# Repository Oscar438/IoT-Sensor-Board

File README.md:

# IoT-Sensor-Board

Eagle uses project files, these are kind of like eagle specific folders where it stores boards and schematics. To use the Git repo you'll want
to add the directory to your eagle path. Go to options>directories and add the gitlibrary folder, and project folder by pasting the path. You 
can add multiple paths by using the semicolon (;)

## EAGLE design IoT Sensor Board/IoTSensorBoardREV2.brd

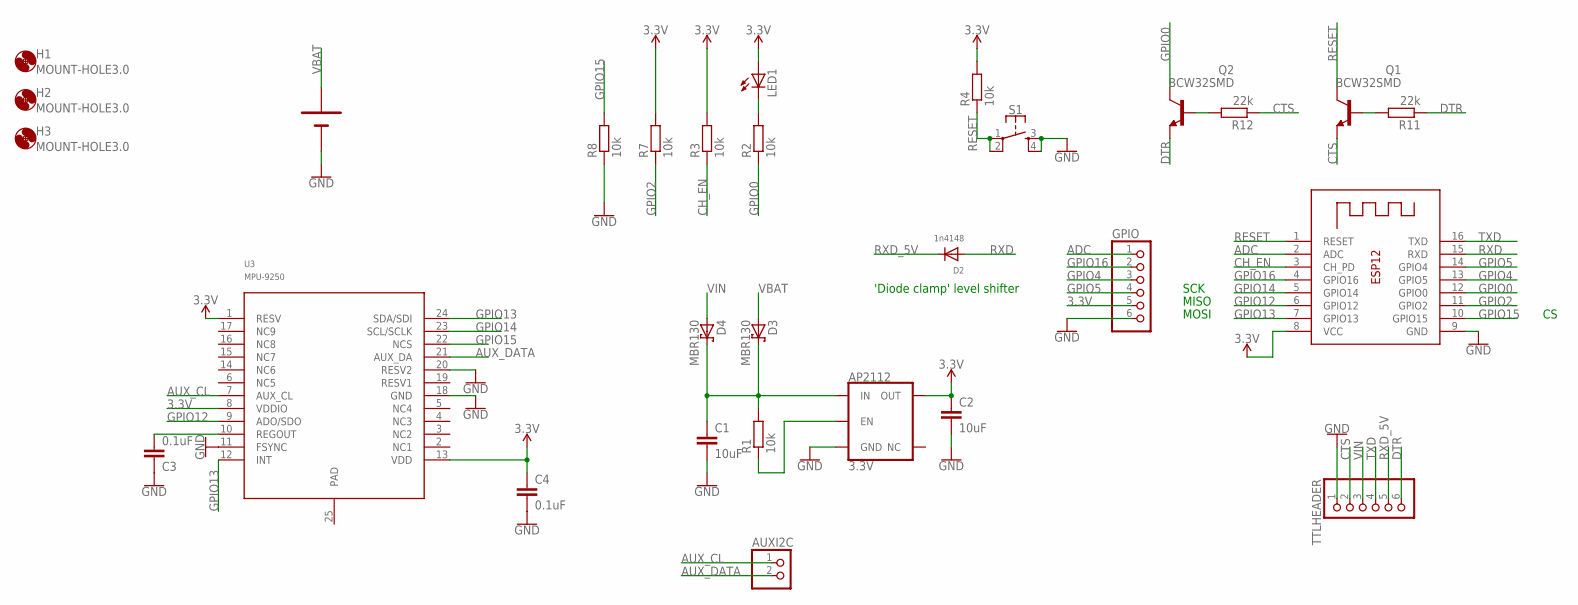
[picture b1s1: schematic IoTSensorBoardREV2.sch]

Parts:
AP2112: 3.3V; SOT23-5
AUXI2C: PINHD-1X2; 1X02
C1, C2: 10uF; C0805
C3, C4: 0.1uF; C0805
D2: 1n4148; SMADIODE
D3, D4: MBR130; SMB
ESP-12: ESP-12
GPIO: PINHD-1X6; 1X06
H1, H2, H3: MOUNT-HOLE3.0; 3,0
LED1: LEDCHIP-LED0805; CHIP-LED0805
Q1, Q2: BCW32SMD; SOT23-BEC
R1, R2, R3, R4, R7, R8: 10k; R0805
R11, R12: 22k; R0805
S1: MOMENTARY-SWITCH-SPST-2-SMD-5.2MM; TACTILE_SWITCH_SMD_5.2MM
TTLHEADER: PINHD-1X6; 1X06
U3: MPU-9250; LEAD-QFN24
U$1: SMTU_2450N

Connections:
3.3V: AP2112.5 (OUT), C2.1, C4.1, ESP-12.8 (VCC), GPIO.5, LED1.A, R3.2, R4.2, R7.2, U3.1 (RESV), U3.8 (VDDIO), U3.13 (VDD)
ADC: ESP-12.2 (ADC), GPIO.1
AUX_CL: AUXI2C.1, U3.7 (AUX_CL)
AUX_DATA: AUXI2C.2, U3.21 (AUX_DA)
CH_EN: ESP-12.3 (CH_PD), R3.1
CTS: Q1.E, R12.1, TTLHEADER.2
DTR: Q2.E, R11.1, TTLHEADER.6
GND: AP2112.2 (GND), C1.2, C2.2, C3.1, C4.2, ESP-12.9 (GND), GPIO.6, R8.1, S1.3, S1.4, TTLHEADER.1, U3.11 (FSYNC), U3.18 (GND), U3.20 (RESV2), U$1.P$1 (P$1N)
GPIO0: ESP-12.12 (GPIO0), Q2.C, R2.1
GPIO2: ESP-12.11 (GPIO2), R7.1
GPIO4: ESP-12.13 (GPIO5), GPIO.3
GPIO5: ESP-12.14 (GPIO4), GPIO.4
GPIO12: ESP-12.6 (GPIO12), U3.9 (ADO/SDO)
GPIO13: ESP-12.7 (GPIO13), U3.12 (INT), U3.24 (SDA/SDI)
GPIO14: ESP-12.5 (GPIO14), U3.23 (SCL/SCLK)
GPIO15: ESP-12.10 (GPIO15), R8.2, U3.22 (NCS)
GPIO16: ESP-12.4 (GPIO16), GPIO.2
unnamed: AP2112.3 (EN), R1.1
unnamed: AP2112.1 (IN), C1.1, D3.C, D4.C, R1.2
unnamed: LED1.C, R2.2
unnamed: C3.2, U3.10 (REGOUT)
unnamed: Q2.B, R12.2
unnamed: Q1.B, R11.2
RESET: ESP-12.1 (RESET), Q1.C, R4.1, S1.1, S1.2
RXD: D2.A, ESP-12.15 (RXD)
RXD_5V: D2.C, TTLHEADER.5
TXD: ESP-12.16 (TXD), TTLHEADER.4
VBAT: D3.A, U$1.P$2 (P$2P)
VIN: D4.A, TTLHEADER.3

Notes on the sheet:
'Diode clamp' level shifter
SCK
MISO
MOSI

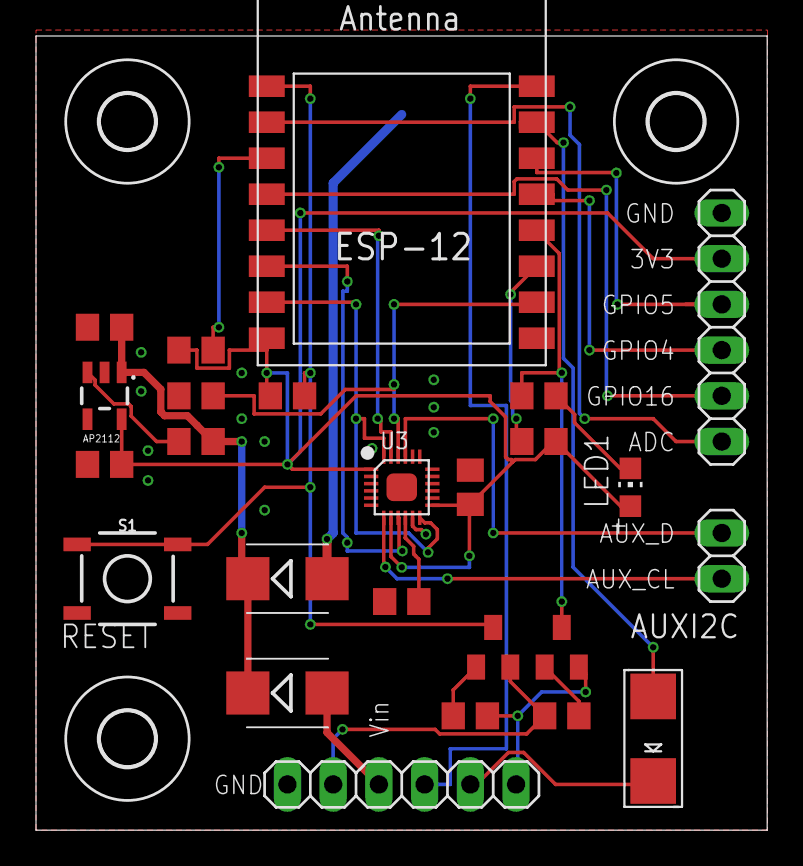
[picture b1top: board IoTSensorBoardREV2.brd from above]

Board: 2 copper layers, 40.6 x 44.1 mm, 29 parts (1 on the bottom side), 29 nets.

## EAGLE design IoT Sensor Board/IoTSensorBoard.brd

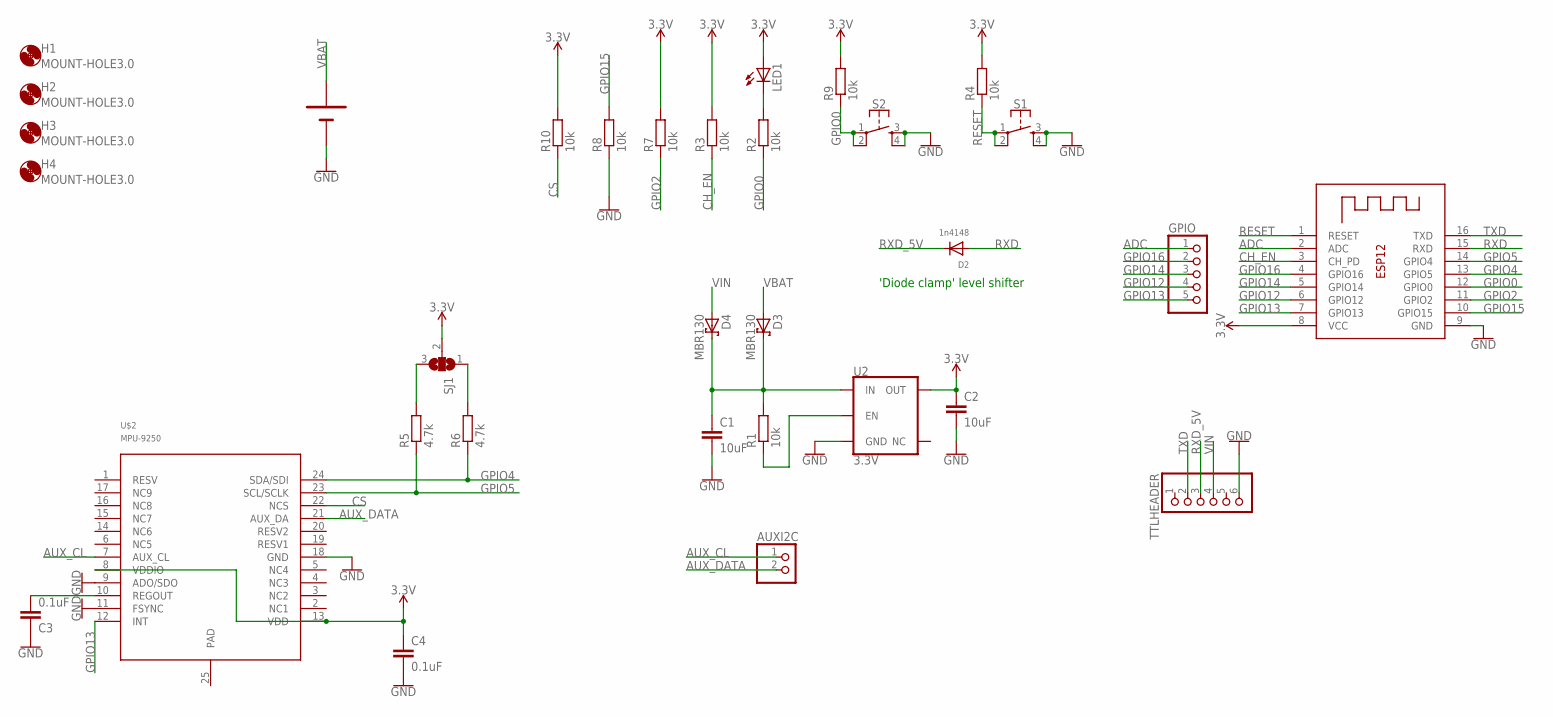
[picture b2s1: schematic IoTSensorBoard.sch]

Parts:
AUXI2C: PINHD-1X2; 1X02
C1, C2: 10uF; C0805
C3, C4: 0.1uF; C0805
D2: 1n4148; SMADIODE
D3, D4: MBR130; SMB
GPIO: PINHD-1X5; 1X05
H1, H2, H3, H4: MOUNT-HOLE3.0; 3,0
LED1: LEDCHIP-LED0805; CHIP-LED0805
R1, R2, R3, R4, R7, R8, R9, R10: 10k; R0805
R5, R6: 4.7k; R0805
S1, S2: MOMENTARY-SWITCH-SPST-2-SMD-5.2MM; TACTILE_SWITCH_SMD_5.2MM
SJ1: SJ2W; SJ_2
TTLHEADER: PINHD-1X6; 1X06
U2: 3.3V; SOT23-5
U$1: SMTU_2450N
U$2: MPU-9250; LEAD-QFN24
X1: ESP-12

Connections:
3.3V: C2.1, C4.1, LED1.A, R3.2, R4.2, R7.2, R9.2, R10.2, SJ1.2, U2.5 (OUT), U$2.8 (VDDIO), U$2.13 (VDD), X1.8 (VCC)
ADC: GPIO.1, X1.2 (ADC)
AUX_CL: AUXI2C.1, U$2.7 (AUX_CL)
AUX_DATA: AUXI2C.2, U$2.21 (AUX_DA)
CH_EN: R3.1, X1.3 (CH_PD)
CS: R10.1, U$2.22 (NCS)
GND: C1.2, C2.2, C3.1, C4.2, R8.1, S1.3, S1.4, S2.3, S2.4, TTLHEADER.6, U2.2 (GND), U$1.P$1 (P$1N), U$2.9 (ADO/SDO), U$2.11 (FSYNC), U$2.18 (GND), X1.9 (GND)
GPIO0: R2.1, R9.1, S2.1, S2.2, X1.12 (GPIO0)
GPIO2: R7.1, X1.11 (GPIO2)
GPIO4: R6.1, U$2.24 (SDA/SDI), X1.13 (GPIO5)
GPIO5: R5.1, U$2.23 (SCL/SCLK), X1.14 (GPIO4)
GPIO12: GPIO.4, X1.6 (GPIO12)
GPIO13: GPIO.5, U$2.12 (INT), X1.7 (GPIO13)
GPIO14: GPIO.3, X1.5 (GPIO14)
GPIO15: R8.2, X1.10 (GPIO15)
GPIO16: GPIO.2, X1.4 (GPIO16)
unnamed: R1.1, U2.3 (EN)
unnamed: C1.1, D3.C, D4.C, R1.2, U2.1 (IN)
unnamed: LED1.C, R2.2
unnamed: R5.2, SJ1.3
unnamed: C3.2, U$2.10 (REGOUT)
unnamed: R6.2, SJ1.1
RESET: R4.1, S1.1, S1.2, X1.1 (RESET)
RXD: D2.A, X1.15 (RXD)
RXD_5V: D2.C, TTLHEADER.3
TXD: TTLHEADER.2, X1.16 (TXD)
VBAT: D3.A, U$1.P$2 (P$2P)
VIN: D4.A, TTLHEADER.4

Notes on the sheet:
'Diode clamp' level shifter

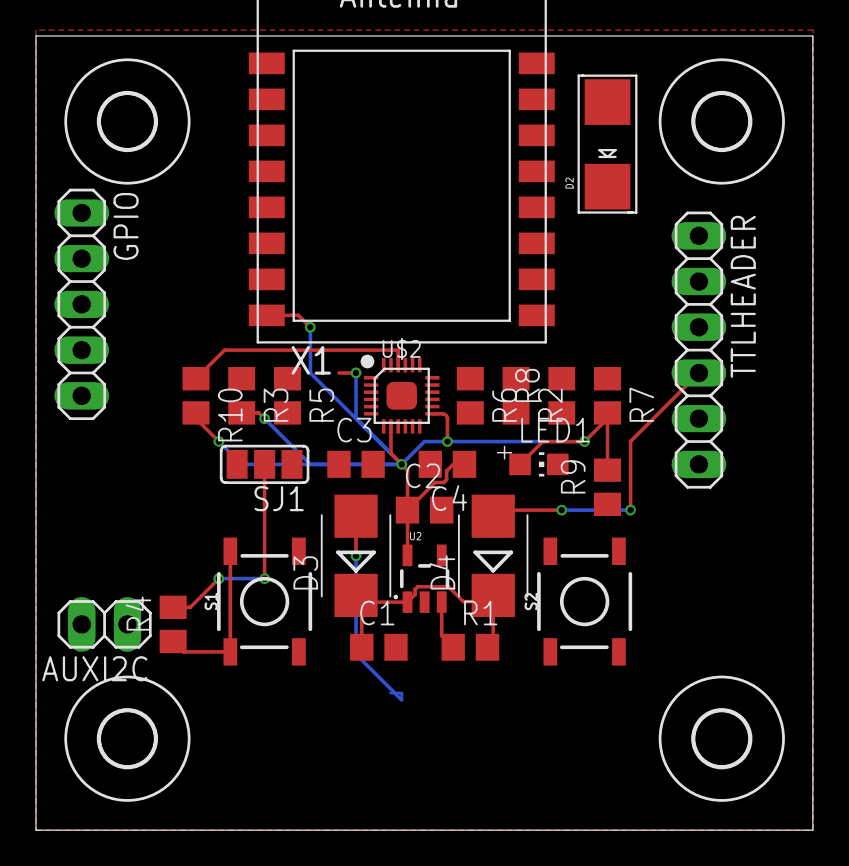
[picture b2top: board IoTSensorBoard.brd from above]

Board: 2 copper layers, 43.2 x 44.1 mm, 32 parts (1 on the bottom side), 28 nets.

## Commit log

2018-05-01 First commit
    Initial commit using eagle files, sparkfun libraries included along with an IoT Custom library for any parts we might need to make ourselves
2018-05-01 Edited readme
2018-05-01 ESP8266 board mostly done schematic wise
2018-05-02 Alain Testing Git
    Added a rubbish .brd file
2018-05-03 Schematic completed
    I had to change the MPU part, the sparkfun version had a chip that wouldn't play nice on the PCB
2018-05-03 ??
    ??
2018-05-05 Revision 2
    Revision 2 Changes:
    MPU-9250 now communicates using SPI
    Addition of two transistors to make use of FDTI breakout board DTR (Data Terminal Ready), and CTS (Clear To Send) pins. Now when programming with an FDTI adaptor the ESP-12s will automaticall reboot 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
    Removed Programming button as it's no longer needed.
    Still needs silkscreen title, and vscores
2018-05-07 Updated REV2
    Silkscreen improved

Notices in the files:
parts and their libraries:
SparkFun-Switches: Licensing: Creative Commons ShareAlike 4.0 International - https://creativecommons.org/licenses/by-sa/4.0
